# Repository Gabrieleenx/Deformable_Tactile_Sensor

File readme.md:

# Deformable In-Hand Slip-Aware Tactile Sensor 

This is the material and guides for the paper "Deformable In-Hand Slip-Aware Tactile Sensor with Integrated Velocity Sensing, Force/Torque and Pressure Map Estimation". You can also find a more popular science presentatin on the entire project https://youtu.be/DqMjxcfm4Ek?si=F0FGEtK1jk1I4O4m

This repo is devided into 3 parts: 
1. build files: this is the files and guide to physically build the sensor 
2. embedded code: this is the code that runs on the sensor
3. code on pc: this is the code on the pc that interfaces with the sensor, it also contains the code for calibrating the sensors. 

A 3D printable version of the gripper used can be found at: https://github.com/Gabrieleenx/Parallel_gripper and the fingers to mount the sensors can be found at "/build_files/fingers_cnc", I CNC them from 6061 aluminium on my own CNC, but they could be ordered from PCBWay.

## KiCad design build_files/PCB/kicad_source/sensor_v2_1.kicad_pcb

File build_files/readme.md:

# Sensor build guide

This is a guide for how to build the sensors. This guide is aimed at people who know how to use tools such as 3D printers, soldering equipment, and basic embedded electronics. This guide is written to a reasonable level of detail, but it is expected that whoever follows it can fill in the gaps.

## PCB

There are two PCB boards that need to be manufactured. I manufactured them as one board, where they could be broken off from each other. The PCB is manufactured as a 4-layer, double-sided board, with machine assembly. It is not designed for manual assembly, except for attaching the optical sensors, which have to be soldered manually. I used PCBWay to manufacture them; other similar services should also work. Under the PCB subfolder, you will find the files necessary for manufacturing and the BOM. The source KiCad files are also provided.

## Optical sensor unit

Each optical sensor unit consists of the lens, sensor, and LED. The sensor and lens are from the PAW3335DB-TZDU kit. The lens has to be manually cut to a smaller size, as shown in the figure below.

As can be seen, there is also a small hole drilled where the LED will be placed. The hole is approximately 2 mm deep, just enough to fit the dome of the LED cap. The sensor and LED are then glued to the lens with super glue. Make sure that no glue gets close to the optical hole of the sensor. The final result should resemble the illustration below.

## Printing of contact pad

The contact pad is printed in TPU85 material with 100% infill and PLA as support material. It was printed on a printer that supports multiple printing nozzles (Prusa XL with 5 tool heads). The print is then paused (this can be programmed in PrusaSlicer) when the slots for the magnets are exposed. Twelve N35 magnets, 1 mm thick and 2 mm in diameter, are placed in the slots with a bit of super glue to keep them from jumping out. I put a drop of glue on the side, then dipped the magnet in the drop and placed it into the slot. For this, I printed a tool, essentially a thing with a magnet on it that can open (magnet is glued to top part), to help pick up and place the magnets (see the supporting_files folder). 

After the magnets have been placed, you should have something like the image below.

After this, the 3D print can continue until it is completed. The PLA support is then removed, leaving you with the contact pad containing 12 magnets.

## Wiring

Wiring the optical sensors to the top PCB board is probably the most tedious task. We begin by wiring the cables to each of the optical sensor modules, as shown in the figure below.

It is very important that the correct type of wire is used. It needs to be thin and have a high strand count. If either of these requirements is not met, the cable will either break during repeated bending or it will not be flexible enough to assemble. I use 30 AWG, 49-strand wire. Also, be careful not to damage the sensor during soldering.

Then, I mark all the cables and place them in the contact pad, as shown below. I add a bit of glue to make sure the sensor won't fall out during operation.

Then the top PCB can be placed.

Finally, solder all the cables. Be careful to solder them correctly, as it is a bit confusing. I used a laptop with KiCad and the datasheets open to find the correct pin matching. Just remember that you are viewing the design from the opposite direction in KiCad. The end result should look something like this:

## Assembly

The final assembly is very simple. You will need three M3 spacers, 5 mm, ([Würth Elektronik 970050366](https://www.mouser.se/en/ProductDetail/Wurth-Elektronik/970050366?qs=wr8lucFkNMUPheOXmFZsfA%3D%3D)) spacers and six M3 screws. I think the top M3 screws are 6 mm long, and the length of the bottom screws will depend on what the assembly will be mounted on. The important thing is that the M3 screws can both fit into the spacers.

And you have your final assembly:

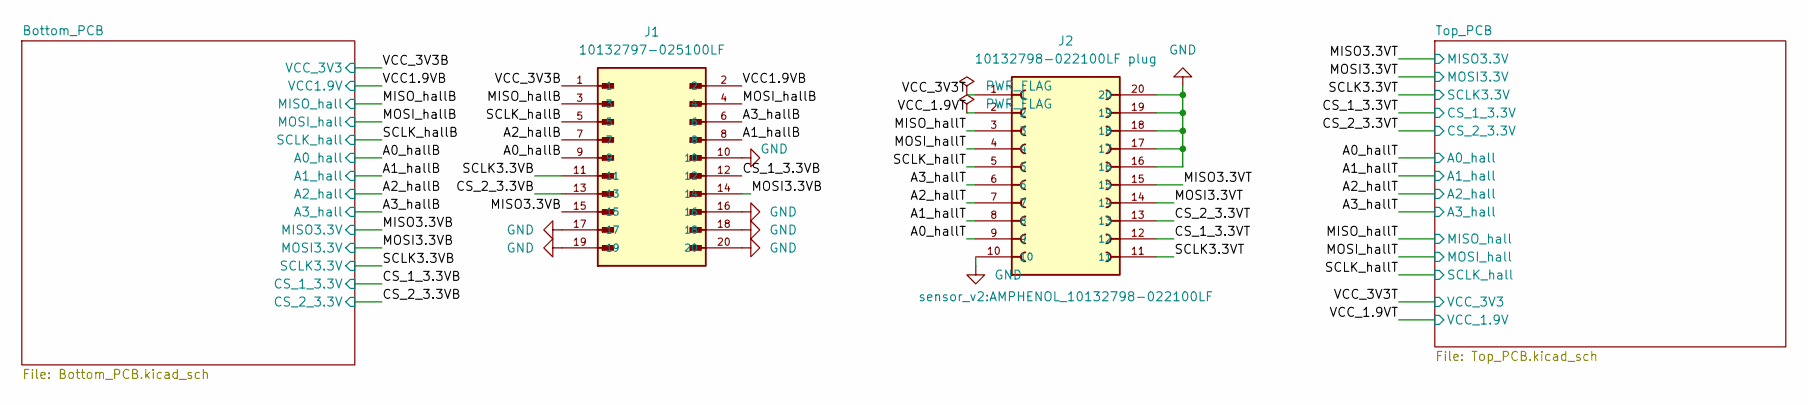
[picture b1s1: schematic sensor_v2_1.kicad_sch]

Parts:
J1: 10132797-025100LF; AMPHENOL_10132797-025100LF; PARTREV F
J2: 10132798-022100LF plug; AMPHENOL_10132798-022100LF; PARTREV F

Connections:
/A0_hallB: J1.9; also elsewhere on the board
/A0_hallT: J2.9; also elsewhere on the board
/A1_hallB: J1.8; also elsewhere on the board
/A1_hallT: J2.8; also elsewhere on the board
/A2_hallB: J1.7; also elsewhere on the board
/A2_hallT: J2.7; also elsewhere on the board
/A3_hallB: J1.6; also elsewhere on the board
/A3_hallT: J2.6; also elsewhere on the board
/CS_1_3.3VB: J1.12; also elsewhere on the board
/CS_1_3.3VT: J2.12; also elsewhere on the board
/CS_2_3.3VB: J1.13; also elsewhere on the board
/CS_2_3.3VT: J2.13; also elsewhere on the board
/MISO3.3VB: J1.15; also elsewhere on the board
/MISO3.3VT: J2.15; also elsewhere on the board
/MISO_hallB: J1.3; also elsewhere on the board
/MISO_hallT: J2.3; also elsewhere on the board
/MOSI3.3VB: J1.14; also elsewhere on the board
/MOSI3.3VT: J2.14; also elsewhere on the board
/MOSI_hallB: J1.4; also elsewhere on the board
/MOSI_hallT: J2.4; also elsewhere on the board
/SCLK3.3VB: J1.11; also elsewhere on the board
/SCLK3.3VT: J2.11; also elsewhere on the board
/SCLK_hallB: J1.5; also elsewhere on the board
/SCLK_hallT: J2.5; also elsewhere on the board
/VCC1.9VB: J1.2; also elsewhere on the board
/VCC_1.9VT: J2.2; also elsewhere on the board
/VCC_3V3B: J1.1; also elsewhere on the board
/VCC_3V3T: J2.1; also elsewhere on the board
GND: J1.10, J1.16, J1.17, J1.18, J1.19, J1.20, J2.10, J2.16, J2.17, J2.18, J2.19, J2.20; also elsewhere on the board

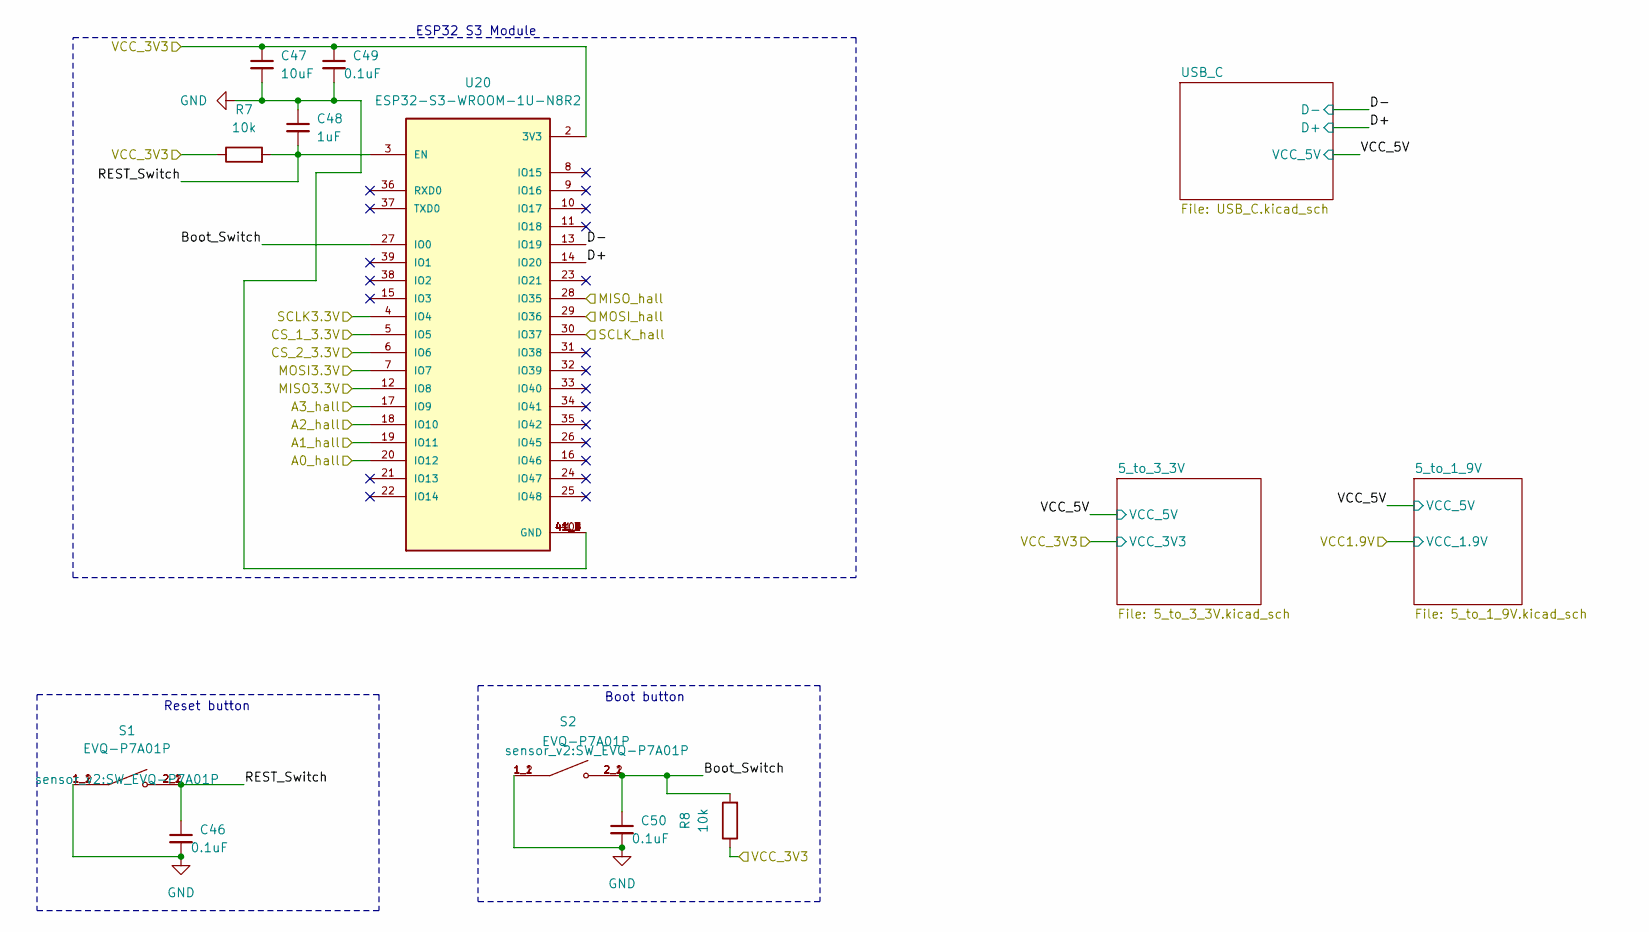
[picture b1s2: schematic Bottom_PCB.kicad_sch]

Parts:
C46, C49, C50: 0.1uF; C_0402_1005Metric; Manifacturer Part Number MLASE105SB7104KFNA01
C47: 10uF; C_0603_1608Metric; Manifacturer Part Number CL10A106KP8NQSC
C48: 1uF; C_0402_1005Metric; Manifacturer Part Number MCASE105SB5105KFNA1J
R7, R8: 10k; R_0402_1005Metric; Manifacturer Part Number TNPW040210K0BHED
S1, S2: EVQ-P7A01P; SW_EVQ-P7A01P; Manifacturer Part Number EVQ-P7A01P
U20: ESP32-S3-WROOM-1U-N8R2; XCVR_ESP32-S3-WROOM-1U-N8R2; PARTREV v1.1

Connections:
/A0_hallB: U20.20 (IO12); also elsewhere on the board
/A1_hallB: U20.19 (IO11); also elsewhere on the board
/A2_hallB: U20.18 (IO10); also elsewhere on the board
/A3_hallB: U20.17 (IO9); also elsewhere on the board
/Bottom_PCB/Boot_Switch: C50.1, R8.2, S2.2_1, S2.2_2, U20.27 (IO0)
/Bottom_PCB/D+: U20.14 (IO20); also elsewhere on the board
/Bottom_PCB/D-: U20.13 (IO19); also elsewhere on the board
/Bottom_PCB/REST_Switch: C46.1, C48.2, R7.2, S1.2_1, S1.2_2, U20.3 (EN)
/CS_1_3.3VB: U20.5 (IO5); also elsewhere on the board
/CS_2_3.3VB: U20.6 (IO6); also elsewhere on the board
/MISO3.3VB: U20.12 (IO8); also elsewhere on the board
/MISO_hallB: U20.28 (IO35); also elsewhere on the board
/MOSI3.3VB: U20.7 (IO7); also elsewhere on the board
/MOSI_hallB: U20.29 (IO36); also elsewhere on the board
/SCLK3.3VB: U20.4 (IO4); also elsewhere on the board
/SCLK_hallB: U20.30 (IO37); also elsewhere on the board
/VCC_3V3B: C47.1, C49.1, R7.1, R8.1, U20.2 (3V3); also elsewhere on the board
GND: C46.2, C47.2, C48.1, C49.2, C50.2, S1.1_1, S1.1_2, S2.1_1, S2.1_2, U20.1 (GND), U20.40 (GND), U20.41_1 (GND), U20.41_2 (GND), U20.41_3 (GND), U20.41_4 (GND), U20.41_5 (GND), U20.41_6 (GND), U20.41_7 (GND), U20.41_8 (GND), U20.41_9 (GND); also elsewhere on the board

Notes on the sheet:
ESP32 S3 Module
Reset button
Boot button

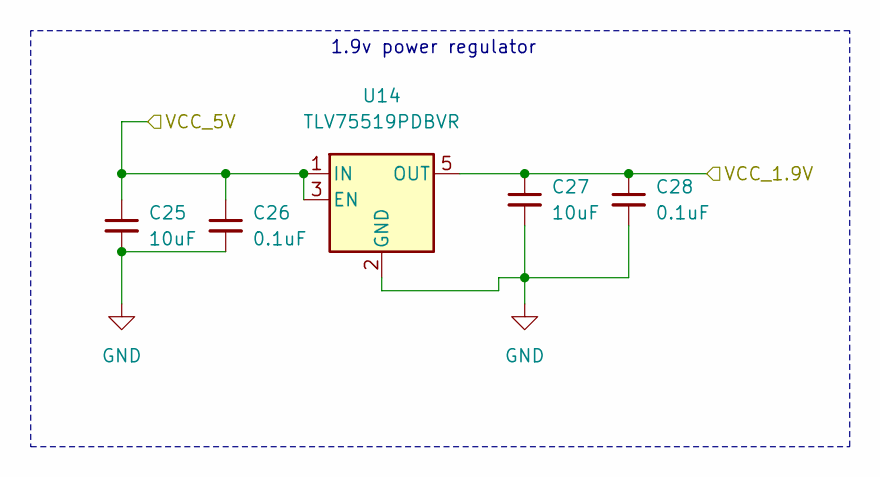
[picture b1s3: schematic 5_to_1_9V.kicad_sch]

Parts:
C25, C27: 10uF; C_0603_1608Metric; Manifacturer Part Number CL10A106KP8NQSC
C26, C28: 0.1uF; C_0402_1005Metric; Manifacturer Part Number MLASE105SB7104KFNA01
U14: TLV75519PDBVR; SOT-23-5; Manifacturer Part Number TLV75519PDBVR

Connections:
/Bottom_PCB/VCC_5V: C25.1, C26.1, U14.1 (IN), U14.3 (EN); also elsewhere on the board
/VCC1.9VB: C27.1, C28.1, U14.5 (OUT); also elsewhere on the board
GND: C25.2, C26.2, C27.2, C28.2, U14.2 (GND); also elsewhere on the board

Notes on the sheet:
1.9v power regulator

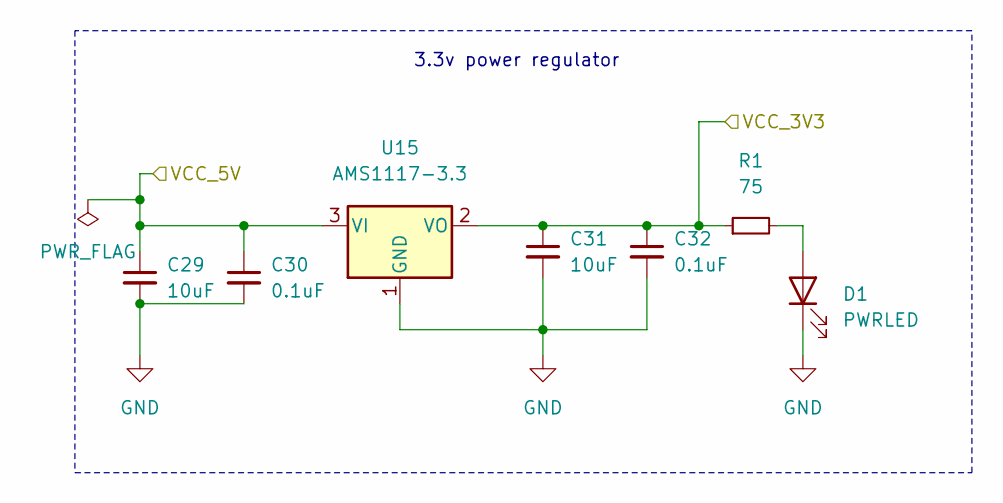
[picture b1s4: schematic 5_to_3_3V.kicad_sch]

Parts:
C29, C31: 10uF; C_0603_1608Metric; Manifacturer Part Number CL10A106KP8NQSC
C30, C32: 0.1uF; C_0402_1005Metric; Manifacturer Part Number MLASE105SB7104KFNA01
D1: PWRLED; LED_0603_1608Metric; Manifacturer Part Number KO EELP41.22-Q1S2-25-A8J8-020-R18
R1: 75; R_0402_1005Metric; Manifacturer Part Number RT0402FRE0775RL
U15: AMS1117-3.3; SOT-223-3_TabPin2; Manifacturer Part Number AMS1117-3.3

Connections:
/Bottom_PCB/VCC_5V: C29.1, C30.1, U15.3 (VI); also elsewhere on the board
/VCC_3V3B: C31.1, C32.1, R1.1, U15.2 (VO); also elsewhere on the board
GND: C29.2, C30.2, C31.2, C32.2, D1.1 (K), U15.1 (GND); also elsewhere on the board
unnamed: D1.2 (A), R1.2

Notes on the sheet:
3.3v power regulator

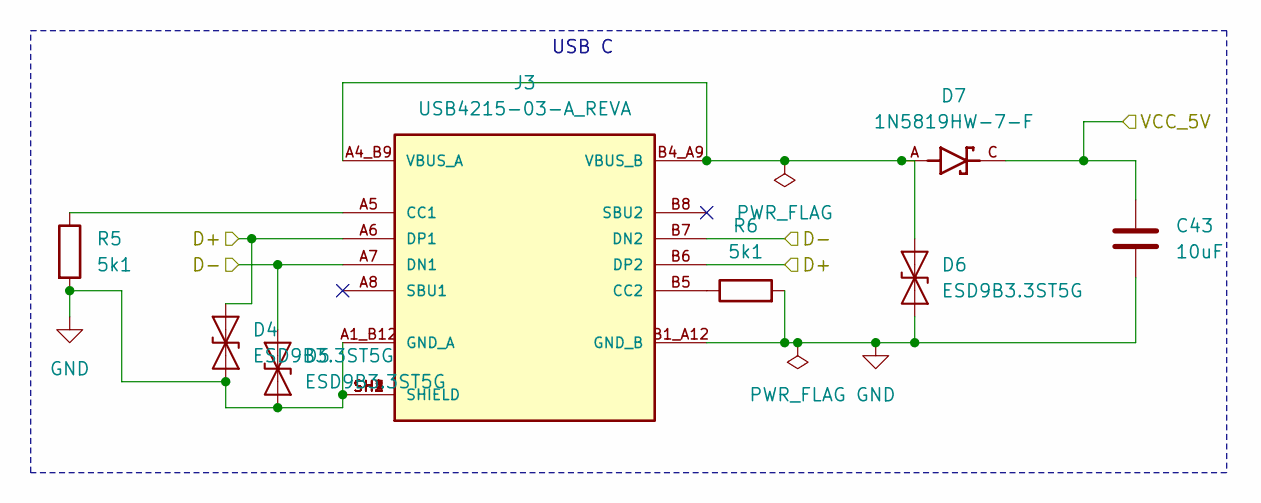
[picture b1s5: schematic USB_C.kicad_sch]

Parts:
C43: 10uF; C_0402_1005Metric; Manifacturer Part Number CL05A106MP8NUB8
D4, D5, D6: ESD9B3.3ST5G; SOD2513X120N; Manifacturer Part Number DESD5V0S1BA-7
D7: 1N5819HW-7-F; SOD3715X145N; PARTREV 18-2
J3: USB4215-03-A_REVA; GCT_USB4215-03-A_REVA; PARTREV A
R5, R6: 5k1; R_0402_1005Metric; Manifacturer Part Number MCS04020C5101FE000

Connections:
/Bottom_PCB/D+: D4.1 (A1), J3.A6 (DP1), J3.B6 (DP2); also elsewhere on the board
/Bottom_PCB/D-: D5.1 (A1), J3.A7 (DN1), J3.B7 (DN2); also elsewhere on the board
/Bottom_PCB/VCC_5V: C43.1, D7.C; also elsewhere on the board
GND: C43.2, D4.2 (A2), D5.2 (A2), D6.1 (A1), J3.A1_B12 (GND_A), J3.B1_A12 (GND_B), J3.SH1 (SHIELD), J3.SH2 (SHIELD), J3.SH3 (SHIELD), J3.SH4 (SHIELD), R5.2, R6.2; also elsewhere on the board
unnamed: D6.2 (A2), D7.A, J3.A4_B9 (VBUS_A), J3.B4_A9 (VBUS_B)
unnamed: J3.A5 (CC1), R5.1
unnamed: J3.B5 (CC2), R6.1

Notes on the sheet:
USB C

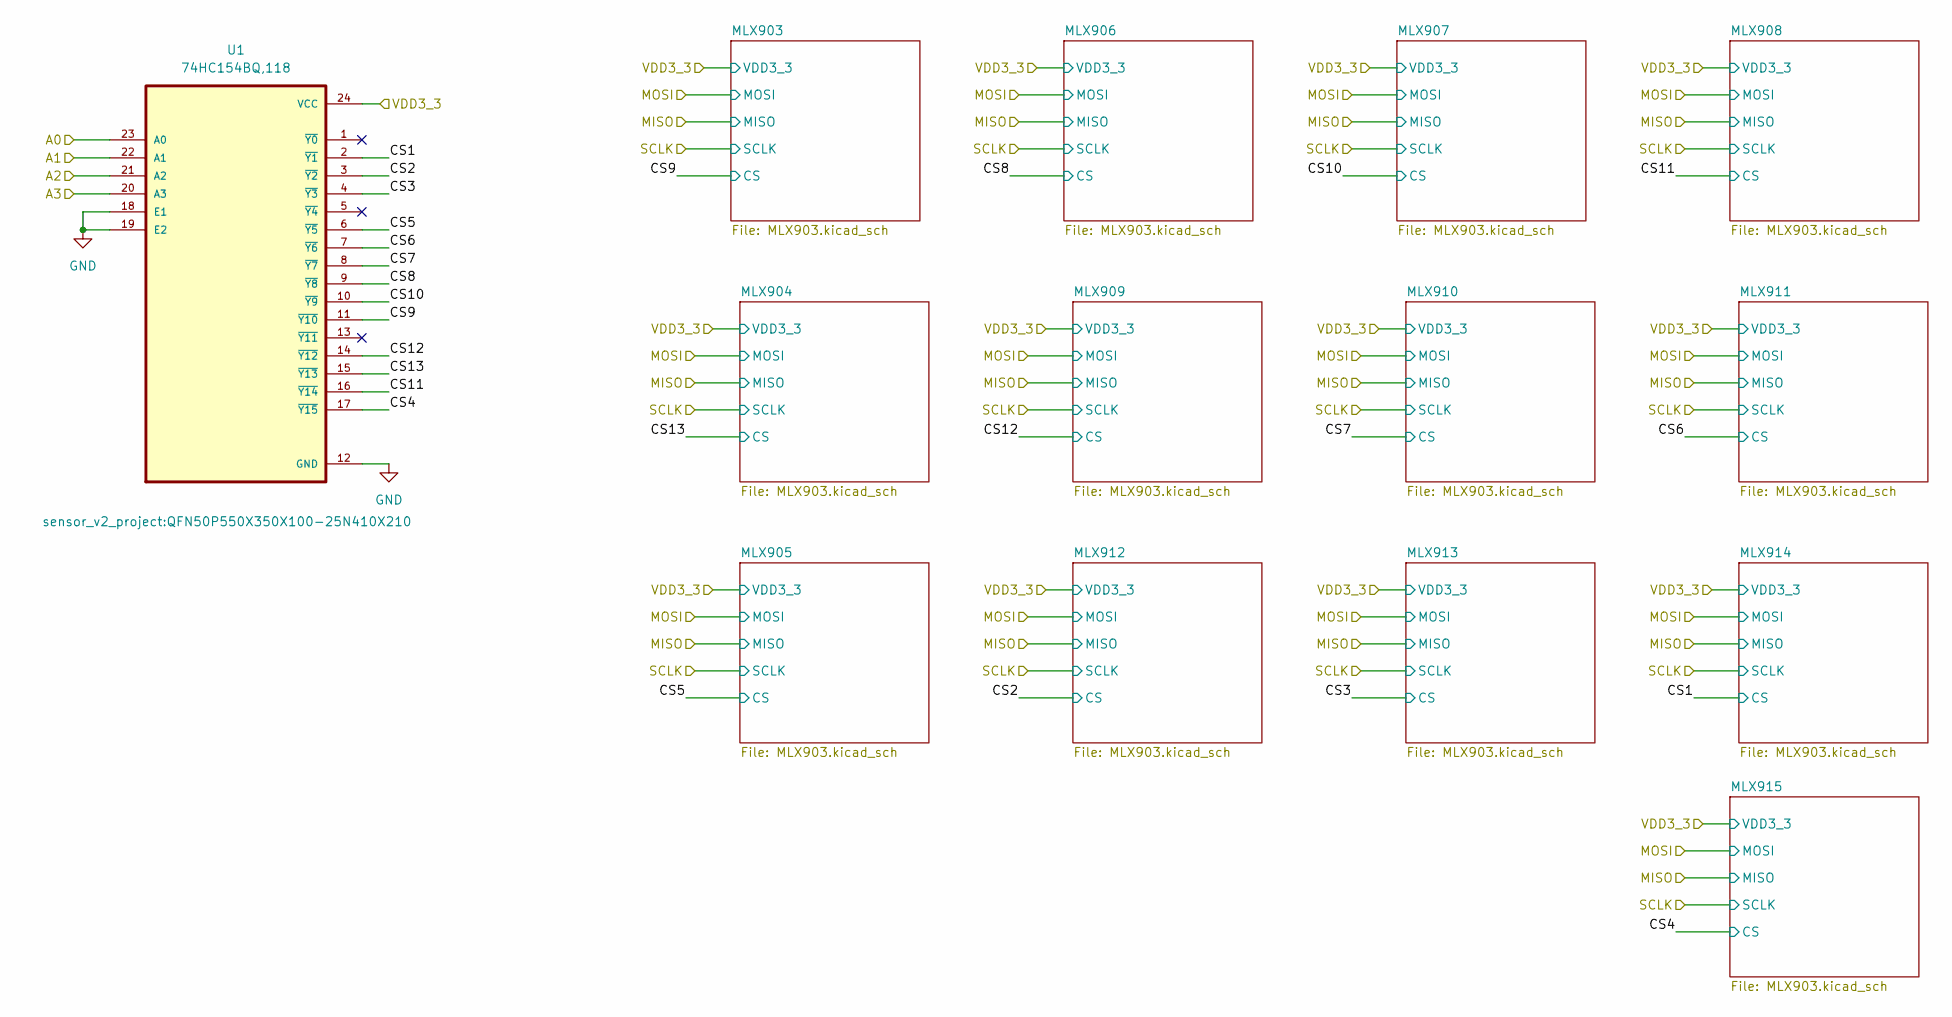
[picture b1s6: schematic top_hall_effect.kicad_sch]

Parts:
U1: 74HC154BQ,118; QFN50P550X350X100-25N410X210; Manifacturer Part Number 74HC154BQ,118

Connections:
/A0_hallT: U1.23 (A0); also elsewhere on the board
/A1_hallT: U1.22 (A1); also elsewhere on the board
/A2_hallT: U1.21 (A2); also elsewhere on the board
/A3_hallT: U1.20 (A3); also elsewhere on the board
/Top_PCB/top_hall_effect/CS1: U1.2 (~Y1); also elsewhere on the board
/Top_PCB/top_hall_effect/CS2: U1.3 (~Y2); also elsewhere on the board
/Top_PCB/top_hall_effect/CS3: U1.4 (~Y3); also elsewhere on the board
/Top_PCB/top_hall_effect/CS4: U1.17 (~Y15); also elsewhere on the board
/Top_PCB/top_hall_effect/CS5: U1.6 (~Y5); also elsewhere on the board
/Top_PCB/top_hall_effect/CS6: U1.7 (~Y6); also elsewhere on the board
/Top_PCB/top_hall_effect/CS7: U1.8 (~Y7); also elsewhere on the board
/Top_PCB/top_hall_effect/CS8: U1.9 (~Y8); also elsewhere on the board
/Top_PCB/top_hall_effect/CS9: U1.11 (~Y10); also elsewhere on the board
/Top_PCB/top_hall_effect/CS10: U1.10 (~Y9); also elsewhere on the board
/Top_PCB/top_hall_effect/CS11: U1.16 (~Y14); also elsewhere on the board
/Top_PCB/top_hall_effect/CS12: U1.14 (~Y12); also elsewhere on the board
/Top_PCB/top_hall_effect/CS13: U1.15 (~Y13); also elsewhere on the board
/VCC_3V3T: U1.24 (VCC); also elsewhere on the board
GND: U1.12 (GND), U1.18 (E1), U1.19 (E2); also elsewhere on the board

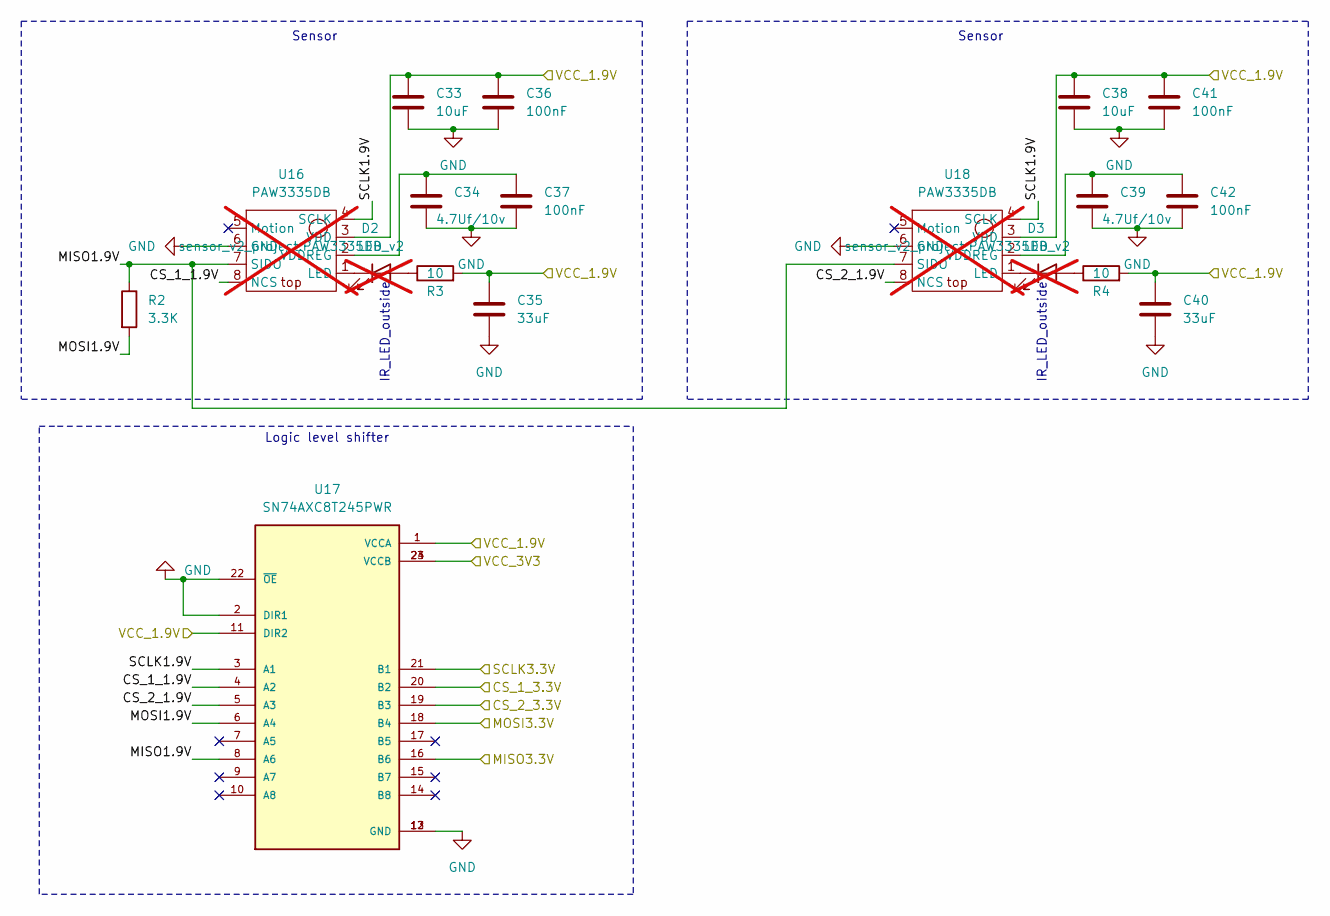
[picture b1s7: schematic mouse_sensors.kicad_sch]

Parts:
C33: 10uF; C_0603_1608Metric; Manifacturer Part Number CL10A106KP8NQSC
C34, C39: 4.7Uf/10v; C_0603_1608Metric; Manifacturer Part Number LMK107BJ475KA-T
C35, C40: 33uF; C_0805_2012Metric; Manifacturer Part Number C2012X5R1A336M125AC
C36, C37, C41, C42: 100nF; C_0402_1005Metric; Manifacturer Part Number MLAST105SB5104KFNA01
C38: 10uF; C_0402_1005Metric; Manifacturer Part Number CL05A106MP8NUB8
D2, D3: LED; LED_0805_2012Metric; Manifacturer Part Number TSMF1030; not fitted
R2: 3.3K; R_0402_1005Metric; Manifacturer Part Number MCS0402MD3301BE000
R3, R4: 10; R_0402_1005Metric; Manifacturer Part Number ERA-2AKD100X
U16, U18: PAW3335DB; PAW3335DB_v2; Manifacturer Part Number No assembly; not fitted
U17: SN74AXC8T245PWR; SOP65P640X120-24N; PARTREV August 2018; DigiKey_Part_Number 296-48831-2-ND

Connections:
/CS_1_3.3VT: U17.20 (B2); also elsewhere on the board
/CS_2_3.3VT: U17.19 (B3); also elsewhere on the board
/MISO3.3VT: U17.16 (B6); also elsewhere on the board
/MOSI3.3VT: U17.18 (B4); also elsewhere on the board
/SCLK3.3VT: U17.21 (B1); also elsewhere on the board
/Top_PCB/mouse_sensors/CS_1_1.9V: U16.8 (NCS), U17.4 (A2)
/Top_PCB/mouse_sensors/CS_2_1.9V: U17.5 (A3), U18.8 (NCS)
/Top_PCB/mouse_sensors/MISO1.9V: R2.1, U16.7 (SIDO), U17.8 (A6), U18.7 (SIDO)
/Top_PCB/mouse_sensors/MOSI1.9V: R2.2, U17.6 (A4)
/Top_PCB/mouse_sensors/SCLK1.9V: U16.4 (SCLK), U17.3 (A1), U18.4 (SCLK)
/VCC_1.9VT: C33.1, C35.1, C36.1, C38.1, C40.1, C41.1, R3.2, R4.2, U16.3 (VDD), U17.1 (VCCA), U17.11 (DIR2), U18.3 (VDD); also elsewhere on the board
/VCC_3V3T: U17.23 (VCCB), U17.24 (VCCB); also elsewhere on the board
GND: C33.2, C34.2, C35.2, C36.2, C37.2, C38.2, C39.2, C40.2, C41.2, C42.2, U16.6 (GND), U17.2 (DIR1), U17.12 (GND), U17.13 (GND), U17.22 (~OE), U18.6 (GND); also elsewhere on the board
unnamed: D2.2 (A), R3.1
unnamed: D2.1 (K), U16.1 (LED)
unnamed: D3.2 (A), R4.1
unnamed: D3.1 (K), U18.1 (LED)
unnamed: C34.1, C37.1, U16.2 (VDDREG)
unnamed: C39.1, C42.1, U18.2 (VDDREG)

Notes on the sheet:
Logic level shifter
Sensor
IR_LED_outside

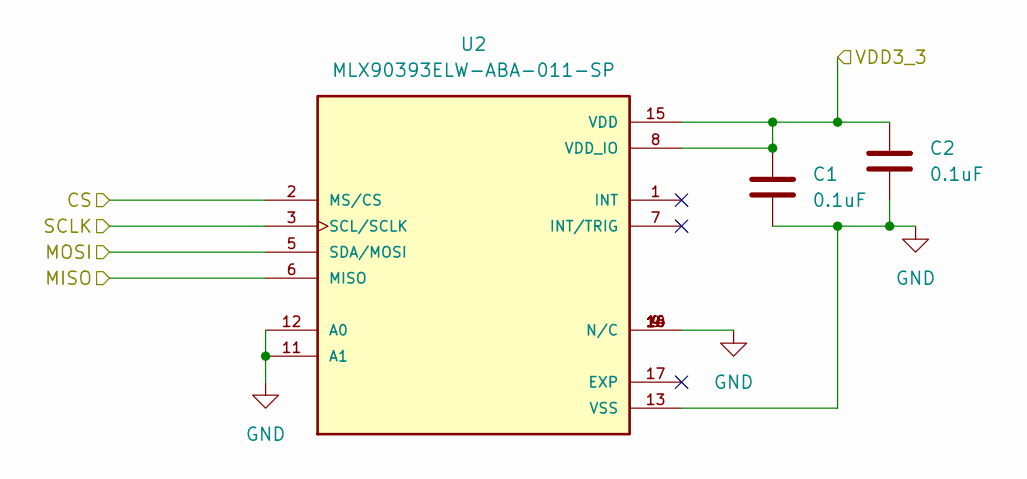
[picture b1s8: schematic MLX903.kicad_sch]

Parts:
C1, C2: 0.1uF; C_0201_0603Metric; Manifacturer Part Number EMK063BJ104KP-F
U2: MLX90393ELW-ABA-011-SP; QFN50P300X300X100-17N; PARTREV 010

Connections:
/MISO_hallT: U2.6 (MISO); also elsewhere on the board
/MOSI_hallT: U2.5 (SDA/MOSI); also elsewhere on the board
/SCLK_hallT: U2.3 (SCL/SCLK); also elsewhere on the board
/Top_PCB/top_hall_effect/CS9: U2.2 (MS/CS); also elsewhere on the board
/VCC_3V3T: C1.1, C2.1, U2.8 (VDD_IO), U2.15 (VDD); also elsewhere on the board
GND: C1.2, C2.2, U2.4 (N/C), U2.9 (N/C), U2.10 (N/C), U2.11 (A1), U2.12 (A0), U2.13 (VSS), U2.14 (N/C), U2.16 (N/C); also elsewhere on the board

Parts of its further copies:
C3, C4, C5, C6, C7, C8, C9, C10, C11, C12, C13, C14, C15, C16, C17, C18, C19, C20, C21, C22, C23, C24, C44, C45: 0.1uF; C_0201_0603Metric; Manifacturer Part Number EMK063BJ104KP-F
U3, U4, U5, U6, U7, U8, U9, U10, U11, U12, U13, U19: MLX90393ELW-ABA-011-SP; QFN50P300X300X100-17N; PARTREV 010

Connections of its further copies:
/MISO_hallT: U3.6 (MISO), U4.6 (MISO), U5.6 (MISO), U6.6 (MISO), U7.6 (MISO), U8.6 (MISO), U9.6 (MISO), U10.6 (MISO), U11.6 (MISO), U12.6 (MISO), U13.6 (MISO), U19.6 (MISO); also elsewhere on the board
/MOSI_hallT: U3.5 (SDA/MOSI), U4.5 (SDA/MOSI), U5.5 (SDA/MOSI), U6.5 (SDA/MOSI), U7.5 (SDA/MOSI), U8.5 (SDA/MOSI), U9.5 (SDA/MOSI), U10.5 (SDA/MOSI), U11.5 (SDA/MOSI), U12.5 (SDA/MOSI), U13.5 (SDA/MOSI), U19.5 (SDA/MOSI); also elsewhere on the board
/SCLK_hallT: U3.3 (SCL/SCLK), U4.3 (SCL/SCLK), U5.3 (SCL/SCLK), U6.3 (SCL/SCLK), U7.3 (SCL/SCLK), U8.3 (SCL/SCLK), U9.3 (SCL/SCLK), U10.3 (SCL/SCLK), U11.3 (SCL/SCLK), U12.3 (SCL/SCLK), U13.3 (SCL/SCLK), U19.3 (SCL/SCLK); also elsewhere on the board
/Top_PCB/top_hall_effect/CS1: U13.2 (MS/CS); also elsewhere on the board
/Top_PCB/top_hall_effect/CS2: U10.2 (MS/CS); also elsewhere on the board
/Top_PCB/top_hall_effect/CS3: U11.2 (MS/CS); also elsewhere on the board
/Top_PCB/top_hall_effect/CS4: U19.2 (MS/CS); also elsewhere on the board
/Top_PCB/top_hall_effect/CS5: U12.2 (MS/CS); also elsewhere on the board
/Top_PCB/top_hall_effect/CS6: U9.2 (MS/CS); also elsewhere on the board
/Top_PCB/top_hall_effect/CS7: U4.2 (MS/CS); also elsewhere on the board
/Top_PCB/top_hall_effect/CS8: U5.2 (MS/CS); also elsewhere on the board
/Top_PCB/top_hall_effect/CS10: U6.2 (MS/CS); also elsewhere on the board
/Top_PCB/top_hall_effect/CS11: U7.2 (MS/CS); also elsewhere on the board
/Top_PCB/top_hall_effect/CS12: U3.2 (MS/CS); also elsewhere on the board
/Top_PCB/top_hall_effect/CS13: U8.2 (MS/CS); also elsewhere on the board
/VCC_3V3T: C3.1, C4.1, C5.1, C6.1, C7.1, C8.1, C9.1, C10.1, C11.1, C12.1, C13.1, C14.1, C15.1, C16.1, C17.1, C18.1, C19.1, C20.1, C21.1, C22.1, C23.1, C24.1, C44.1, C45.1, U3.8 (VDD_IO), U3.15 (VDD), U4.8 (VDD_IO), U4.15 (VDD), U5.8 (VDD_IO), U5.15 (VDD), U6.8 (VDD_IO), U6.15 (VDD), U7.8 (VDD_IO), U7.15 (VDD), U8.8 (VDD_IO), U8.15 (VDD), U9.8 (VDD_IO), U9.15 (VDD), U10.8 (VDD_IO), U10.15 (VDD), U11.8 (VDD_IO), U11.15 (VDD), U12.8 (VDD_IO), U12.15 (VDD), U13.8 (VDD_IO), U13.15 (VDD), U19.8 (VDD_IO), U19.15 (VDD); also elsewhere on the board
GND: C3.2, C4.2, C5.2, C6.2, C7.2, C8.2, C9.2, C10.2, C11.2, C12.2, C13.2, C14.2, C15.2, C16.2, C17.2, C18.2, C19.2, C20.2, C21.2, C22.2, C23.2, C24.2, C44.2, C45.2, U3.4 (N/C), U3.9 (N/C), U3.10 (N/C), U3.11 (A1), U3.12 (A0), U3.13 (VSS), U3.14 (N/C), U3.16 (N/C), U4.4 (N/C), U4.9 (N/C), U4.10 (N/C), U4.11 (A1), U4.12 (A0), U4.13 (VSS), U4.14 (N/C), U4.16 (N/C), U5.4 (N/C), U5.9 (N/C), U5.10 (N/C), U5.11 (A1), U5.12 (A0), U5.13 (VSS), U5.14 (N/C), U5.16 (N/C), U6.4 (N/C), U6.9 (N/C), U6.10 (N/C), U6.11 (A1), U6.12 (A0), U6.13 (VSS), U6.14 (N/C), U6.16 (N/C), U7.4 (N/C), U7.9 (N/C), U7.10 (N/C), U7.11 (A1), U7.12 (A0), U7.13 (VSS), U7.14 (N/C), U7.16 (N/C), U8.4 (N/C), U8.9 (N/C), U8.10 (N/C), U8.11 (A1), U8.12 (A0), U8.13 (VSS), U8.14 (N/C), U8.16 (N/C), U9.4 (N/C), U9.9 (N/C), U9.10 (N/C), U9.11 (A1), U9.12 (A0), U9.13 (VSS), U9.14 (N/C), U9.16 (N/C), U10.4 (N/C), U10.9 (N/C), U10.10 (N/C), U10.11 (A1), U10.12 (A0), U10.13 (VSS), U10.14 (N/C), U10.16 (N/C), U11.4 (N/C), U11.9 (N/C), U11.10 (N/C), U11.11 (A1), U11.12 (A0), U11.13 (VSS), U11.14 (N/C), U11.16 (N/C), U12.4 (N/C), U12.9 (N/C), U12.10 (N/C), U12.11 (A1), U12.12 (A0), U12.13 (VSS), U12.14 (N/C), U12.16 (N/C), U13.4 (N/C), U13.9 (N/C), U13.10 (N/C), U13.11 (A1), U13.12 (A0), U13.13 (VSS), U13.14 (N/C), U13.16 (N/C), U19.4 (N/C), U19.9 (N/C), U19.10 (N/C), U19.11 (A1), U19.12 (A0), U19.13 (VSS), U19.14 (N/C), U19.16 (N/C); also elsewhere on the board

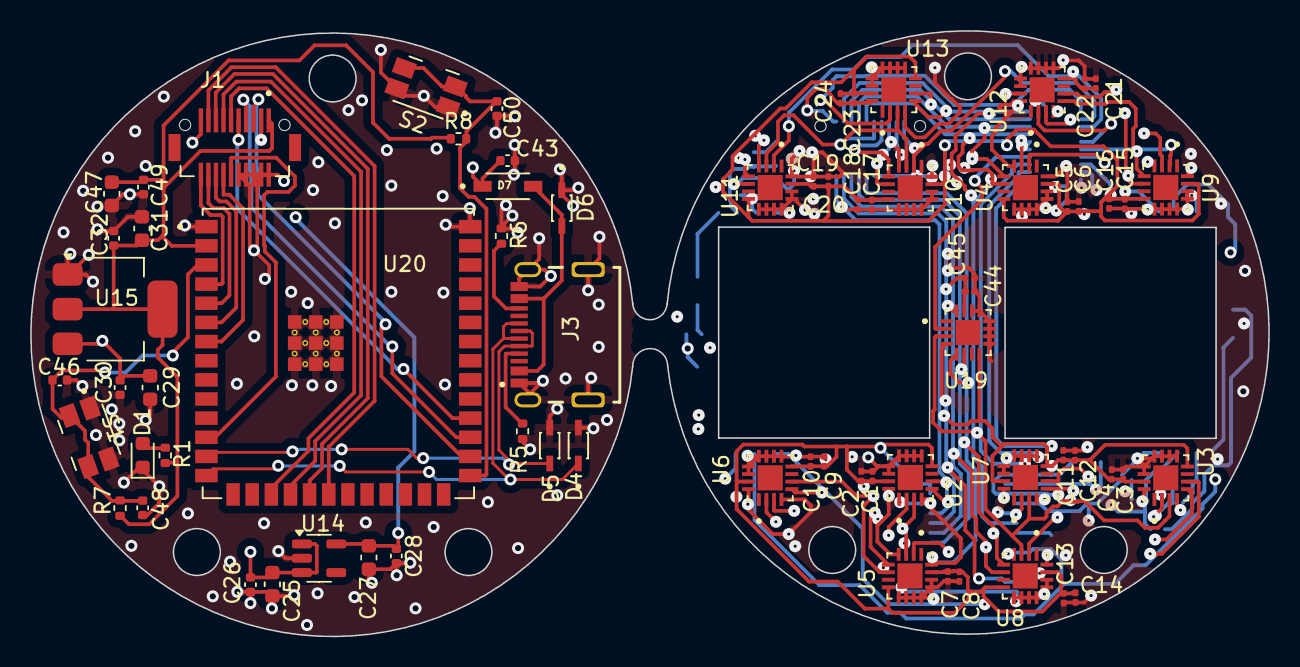
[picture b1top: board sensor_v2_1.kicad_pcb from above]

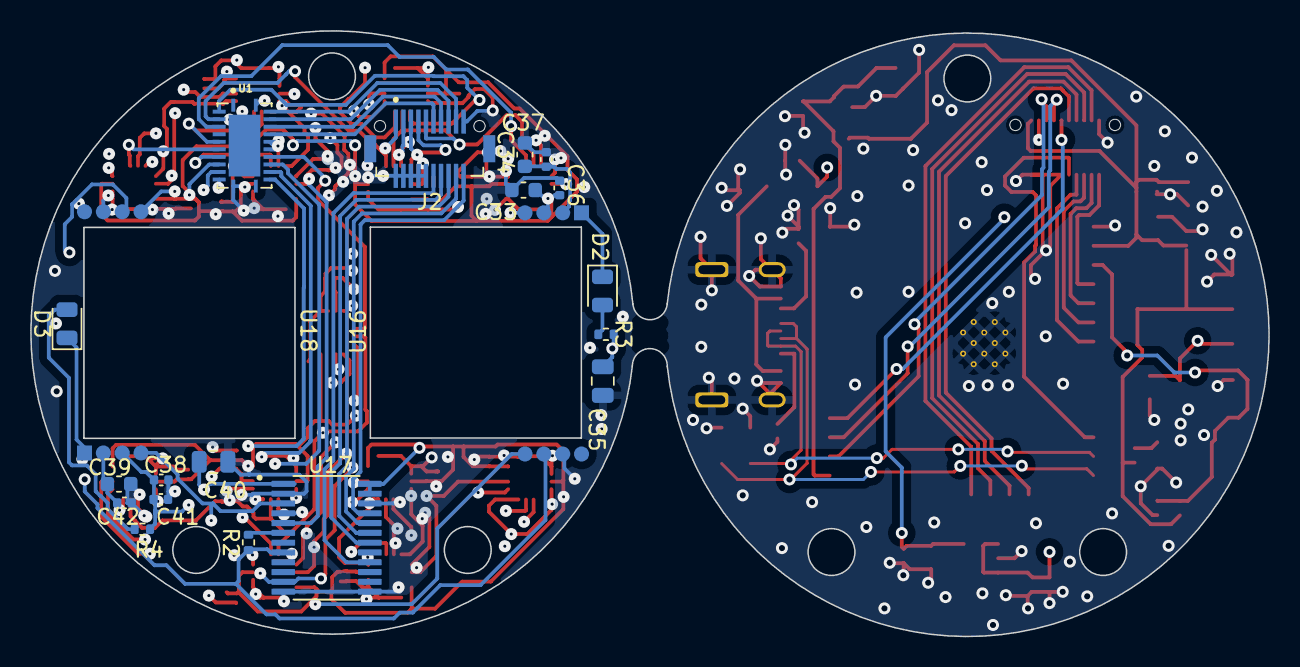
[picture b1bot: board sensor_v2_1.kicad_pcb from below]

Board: 4 copper layers, 82.1 x 40.2 mm, 90 parts (20 on the bottom side), 62 nets.
